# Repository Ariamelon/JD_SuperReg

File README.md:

# Jung-Didden Super Regulator
High performance dual linear power supply.

## Disclaimer
This power supply is based on Walt Jung and Jan Didden's [Super Regulator](https://linearaudio.nl/superregs) design.

## Changelog
* 05/10/2023: Changed output voltage to 15V.
* 27/09/2023: Changed board to 4 layers. Removed fuses. Added MOV surge protection and resistors for RC input filter.
* 25/09/2023: Initial public upload.

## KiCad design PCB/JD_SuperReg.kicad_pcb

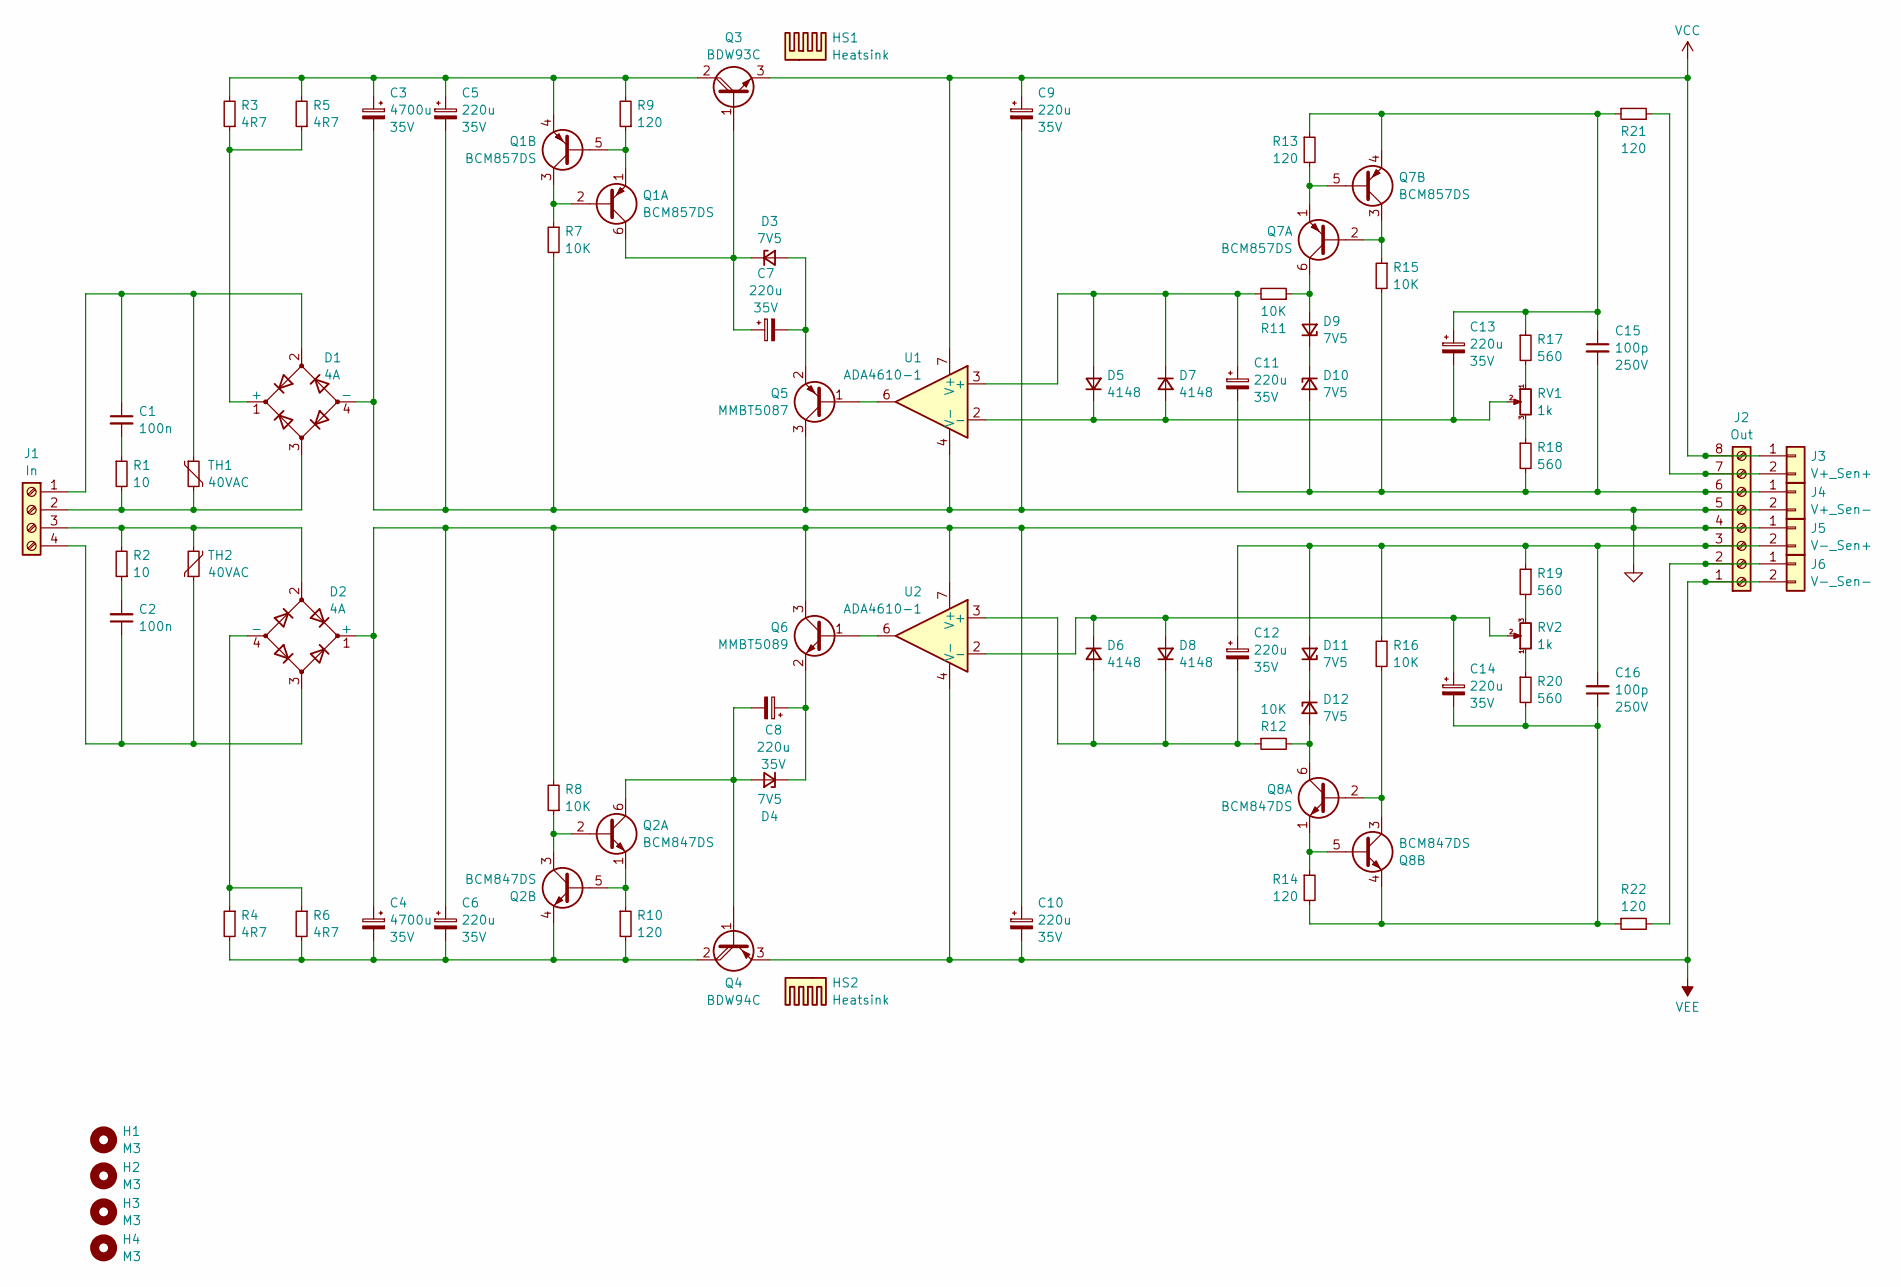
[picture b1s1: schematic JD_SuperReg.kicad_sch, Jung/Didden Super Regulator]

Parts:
C1, C2: 100n; C_1206_3216Metric; Voltage 100V
C3, C4: 4700u; CP_Radial_D18.0mm_P7.50mm; Voltage 35V
C5, C6, C7, C8, C9, C10, C11, C12, C13, C14: 220u; CP_Radial_D8.0mm_P3.50mm; Voltage 35V
C15, C16: 100p; C_0805_2012Metric; Voltage 250V
D1, D2: 4A; Diode_Bridge_Vishay_GBU
D3, D4, D9, D10, D11, D12: 7V5; D_SOD-123
D5, D6, D7, D8: 4148; D_SOD-123
H1, H2, H3, H4: M3; MountingHole_3.2mm_M3_Pad
HS1, HS2: Heatsink
J1: In; TerminalBlock_Phoenix_MKDS-1,5-4-5.08_1x04_P5.08mm_Horizont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
J2: Out; TerminalBlock_Phoenix_MKDS-1,5-8-5.08_1x08_P5.08mm_Horizont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
J3: V+_Sen+; PinHeader_1x02_P2.54mm_Vertical_Jumper
J4: V+_Sen-; PinHeader_1x02_P2.54mm_Vertical_Jumper
J5: V-_Sen+; PinHeader_1x02_P2.54mm_Vertical_Jumper
J6: V-_Sen-; PinHeader_1x02_P2.54mm_Vertical_Jumper
Q1, Q7: BCM857DS; SOT-23-6
Q2, Q8: BCM847DS; SOT-23-6
Q3: BDW93C; TO-220-3_TO-247_Combined_Vertical
Q4: BDW94C; TO-220-3_TO-247_Combined_Vertical
Q5: MMBT5087; SOT-23-3
Q6: MMBT5089; SOT-23-3
R1, R2: 10; R_MiniMELF_MMA-0204
R3, R4, R5, R6: 4R7; R_Axial_DIN0617_L17.0mm_D6.0mm_P20.32mm_Horizontal
R7, R8, R11, R12, R15, R16: 10K; R_MiniMELF_MMA-0204
R9, R10, R13, R14, R21, R22: 120; R_MiniMELF_MMA-0204
R17, R18, R19, R20: 560; R_MiniMELF_MMA-0204
RV1, RV2: 1k; Potentiometer_Bourns_3266W_Vertical
TH1, TH2: 40VAC; RV_Disc_D9mm_W5.2mm_P5mm
U1, U2: ADA4610-1; SOIC-8_3.9x4.9mm_P1.27mm

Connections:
GND: C3.2, C4.1, C5.2, C6.1, C9.2, C10.1, D1.4 (-), D2.1 (+), J2.4, J2.5, J4.2, J5.1, Q5.3 (C), Q6.3 (C), R7.2, R8.2, U1.4 (V-), U2.7 (V+)
unnamed: C1.2, R1.1
unnamed: C2.2, R2.1
unnamed: D1.1 (+), R3.1, R5.1
unnamed: D2.4 (-), R4.1, R6.1
unnamed: C7.2, D3.2 (A), Q5.2 (E)
unnamed: C7.1, D3.1 (K), Q1.6 (C1), Q3.1 (B)
unnamed: C8.2, D4.2 (A), Q2.6 (C1), Q4.1 (B)
unnamed: C8.1, D4.1 (K), Q6.2 (E)
unnamed: C11.1, D5.2 (A), D7.1 (K), R11.2, U1.3 (+)
unnamed: C13.2, D5.1 (K), D7.2 (A), RV1.2, U1.2 (-)
unnamed: C12.2, D6.2 (A), D8.1 (K), R12.1, U2.3 (+)
unnamed: C14.1, D6.1 (K), D8.2 (A), RV2.2, U2.2 (-)
unnamed: D9.2 (A), Q7.6 (C1), R11.1
unnamed: C11.2, C15.2, D10.2 (A), J2.6, J4.1, R15.2, R18.2
unnamed: D9.1 (K), D10.1 (K)
unnamed: C12.1, C16.2, D11.2 (A), J2.3, J5.2, R16.1, R19.1
unnamed: D11.1 (K), D12.1 (K)
unnamed: D12.2 (A), Q8.6 (C1), R12.2
unnamed: C1.1, D1.2, J1.1, TH1.1
unnamed: D1.3, J1.2, R1.2, TH1.2
unnamed: D2.2, J1.3, R2.2, TH2.2
unnamed: C2.1, D2.3, J1.4, TH2.1
unnamed: J2.2, J6.1, R22.2
unnamed: J2.7, J3.2, R21.2
unnamed: Q1.2 (B1), Q1.3 (C2), R7.1
unnamed: Q1.1 (E1), Q1.5 (B2), R9.1
unnamed: C3.1, C5.1, Q1.4 (E2), Q3.2 (C), R3.2, R5.2, R9.2
unnamed: Q2.2 (B1), Q2.3 (C2), R8.1
unnamed: Q2.1 (E1), Q2.5 (B2), R10.1
unnamed: C4.2, C6.2, Q2.4 (E2), Q4.2 (C), R4.2, R6.2, R10.2
unnamed: Q5.1 (B), U1.6
unnamed: Q6.1 (B), U2.6
unnamed: Q7.2 (B1), Q7.3 (C2), R15.1
unnamed: Q7.1 (E1), Q7.5 (B2), R13.2
unnamed: C13.1, C15.1, Q7.4 (E2), R13.1, R17.1, R21.1
unnamed: Q8.2 (B1), Q8.3 (C2), R16.2
unnamed: Q8.1 (E1), Q8.5 (B2), R14.1
unnamed: C14.2, C16.1, Q8.4 (E2), R14.2, R20.2, R22.1
unnamed: R17.2, RV1.1
unnamed: R18.1, RV1.3
unnamed: R19.2, RV2.3
unnamed: R20.1, RV2.1
VCC: C9.1, J2.8, J3.1, Q3.3 (E), U1.7 (V+)
VEE: C10.2, J2.1, J6.2, Q4.3 (E), U2.4 (V-)

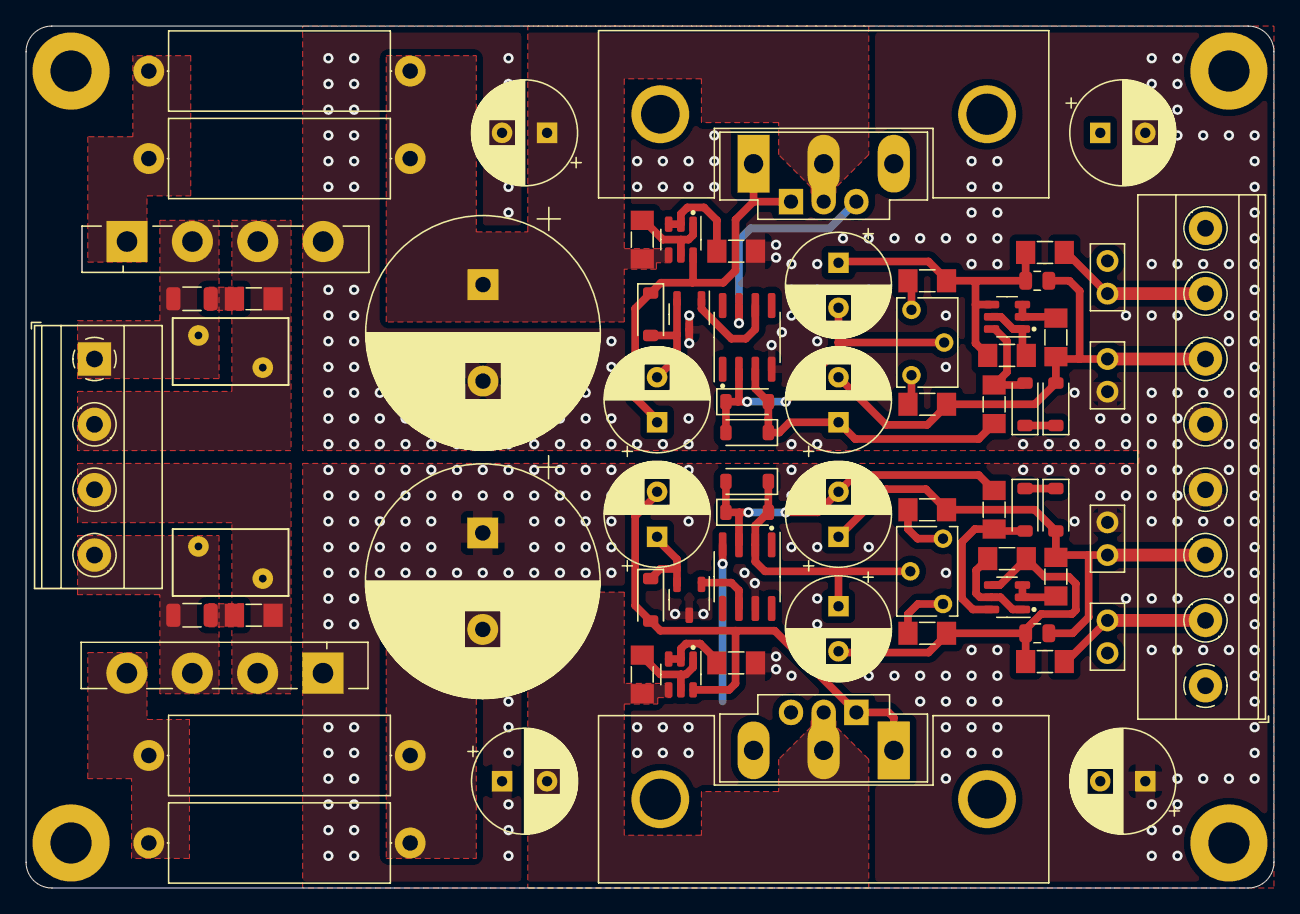
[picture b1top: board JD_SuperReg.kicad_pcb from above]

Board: 4 copper layers, 97.0 x 67.0 mm, 76 parts (0 on the bottom side), 45 nets.

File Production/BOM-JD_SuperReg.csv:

Comment,Designator,Footprint,LCSC
560,R19,R_MiniMELF_MMA-0204,
560,R20,R_MiniMELF_MMA-0204,
120,R22,R_MiniMELF_MMA-0204,
220u,C5,CP_Radial_D8.0mm_P3.50mm,
Heatsink,HS2,Heatsink,
120,R10,R_MiniMELF_MMA-0204,
100n,C2,C_1206_3216Metric,
220u,C12,CP_Radial_D8.0mm_P3.50mm,
120,R21,R_MiniMELF_MMA-0204,
10K,R16,R_MiniMELF_MMA-0204,
BCM847DS,Q2,SOT-23-6,
V-_Sen+,J5,PinHeader_1x02_P2.54mm_Vertical_Jumper,
1k,RV1,Potentiometer_Bourns_3266W_Vertical,
BDW93C,Q3,TO-220-3_TO-247_Combined_Vertical,
10K,R8,R_MiniMELF_MMA-0204,
BCM857DS,Q7,SOT-23-6,
4R7,R6,R_Axial_DIN0617_L17.0mm_D6.0mm_P20.32mm_Horizontal,
220u,C11,CP_Radial_D8.0mm_P3.50mm,
40VAC,TH1,RV_Disc_D9mm_W5.2mm_P5mm,
10K,R15,R_MiniMELF_MMA-0204,
10,R2,R_MiniMELF_MMA-0204,
220u,C10,CP_Radial_D8.0mm_P3.50mm,
220u,C9,CP_Radial_D8.0mm_P3.50mm,
4700u,C3,CP_Radial_D18.0mm_P7.50mm,
120,R14,R_MiniMELF_MMA-0204,
220u,C14,CP_Radial_D8.0mm_P3.50mm,
7V5,D11,D_SOD-123,
7V5,D10,D_SOD-123,
10K,R7,R_MiniMELF_MMA-0204,
V+_Sen-,J4,PinHeader_1x02_P2.54mm_Vertical_Jumper,
7V5,D9,D_SOD-123,
4148,D6,D_SOD-123,
120,R13,R_MiniMELF_MMA-0204,
MMBT5087,Q5,SOT-23-3,
7V5,D3,D_SOD-123,
BCM847DS,Q8,SOT-23-6,
100p,C16,C_0805_2012Metric,
Out,J2,"TerminalBlock_Phoenix_MKDS-1,5-8-5.08_1x08_P5.08mm_Horizontal",
ADA4610-1,U2,SOIC-8_3.9x4.9mm_P1.27mm,
1k,RV2,Potentiometer_Bourns_3266W_Vertical,
V-_Sen-,J6,PinHeader_1x02_P2.54mm_Vertical_Jumper,
Heatsink,HS1,Heatsink,
10,R1,R_MiniMELF_MMA-0204,
10K,R11,R_MiniMELF_MMA-0204,
In,J1,"TerminalBlock_Phoenix_MKDS-1,5-4-5.08_1x04_P5.08mm_Horizontal",
4148,D7,D_SOD-123,
4A,D2,Diode_Bridge_Vishay_GBU,
V+_Sen+,J3,PinHeader_1x02_P2.54mm_Vertical_Jumper,
BCM857DS,Q1,SOT-23-6,
4700u,C4,CP_Radial_D18.0mm_P7.50mm,
220u,C6,CP_Radial_D8.0mm_P3.50mm,
40VAC,TH2,RV_Disc_D9mm_W5.2mm_P5mm,
560,R17,R_MiniMELF_MMA-0204,
100p,C15,C_0805_2012Metric,
4R7,R4,R_Axial_DIN0617_L17.0mm_D6.0mm_P20.32mm_Horizontal,
7V5,D12,D_SOD-123,
BDW94C,Q4,TO-220-3_TO-247_Combined_Vertical,
220u,C8,CP_Radial_D8.0mm_P3.50mm,
10K,R12,R_MiniMELF_MMA-0204,
4R7,R3,R_Axial_DIN0617_L17.0mm_D6.0mm_P20.32mm_Horizontal,
4148,D5,D_SOD-123,
100n,C1,C_1206_3216Metric,
560,R18,R_MiniMELF_MMA-0204,
ADA4610-1,U1,SOIC-8_3.9x4.9mm_P1.27mm,
220u,C13,CP_Radial_D8.0mm_P3.50mm,
120,R9,R_MiniMELF_MMA-0204,
4R7,R5,R_Axial_DIN0617_L17.0mm_D6.0mm_P20.32mm_Horizontal,
220u,C7,CP_Radial_D8.0mm_P3.50mm,
4A,D1,Diode_Bridge_Vishay_GBU,
4148,D8,D_SOD-123,
7V5,D4,D_SOD-123,
MMBT5089,Q6,SOT-23-3,

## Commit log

2023-09-24 Finalized layout
2023-09-25 Initial public upload
2023-09-27 27/09/2023 update
    Changed board to 4 layers. Removed fuses. Added MOV surge protection and resistors for RC input filter.
2023-10-05 05/10/2023 update
    Changed output voltage to 15V.
